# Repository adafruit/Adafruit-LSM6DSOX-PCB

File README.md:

## Adafruit LSM6DSOX 6-DoF Accelerometer and Gyro PCB

<a href="http://www.adafruit.com/products/4438"><br/>
Click here to purchase one from the Adafruit shop</a>

PCB files for the Adafruit LSM6DSOX 6-DoF Accelerometer and Gyro. 

Format is EagleCAD schematic and board layout
* https://www.adafruit.com/product/4438

### Description

INSERT PRODUCT COPY HERE

### License

Adafruit invests time and resources providing this open source design, please support Adafruit and open-source hardware by purchasing products from [Adafruit](https://www.adafruit.com)!

Designed by Bryan Siepert for Adafruit Industries.

Creative Commons Attribution/Share-Alike, all text above must be included in any redistribution. 
See license.txt for additional details.

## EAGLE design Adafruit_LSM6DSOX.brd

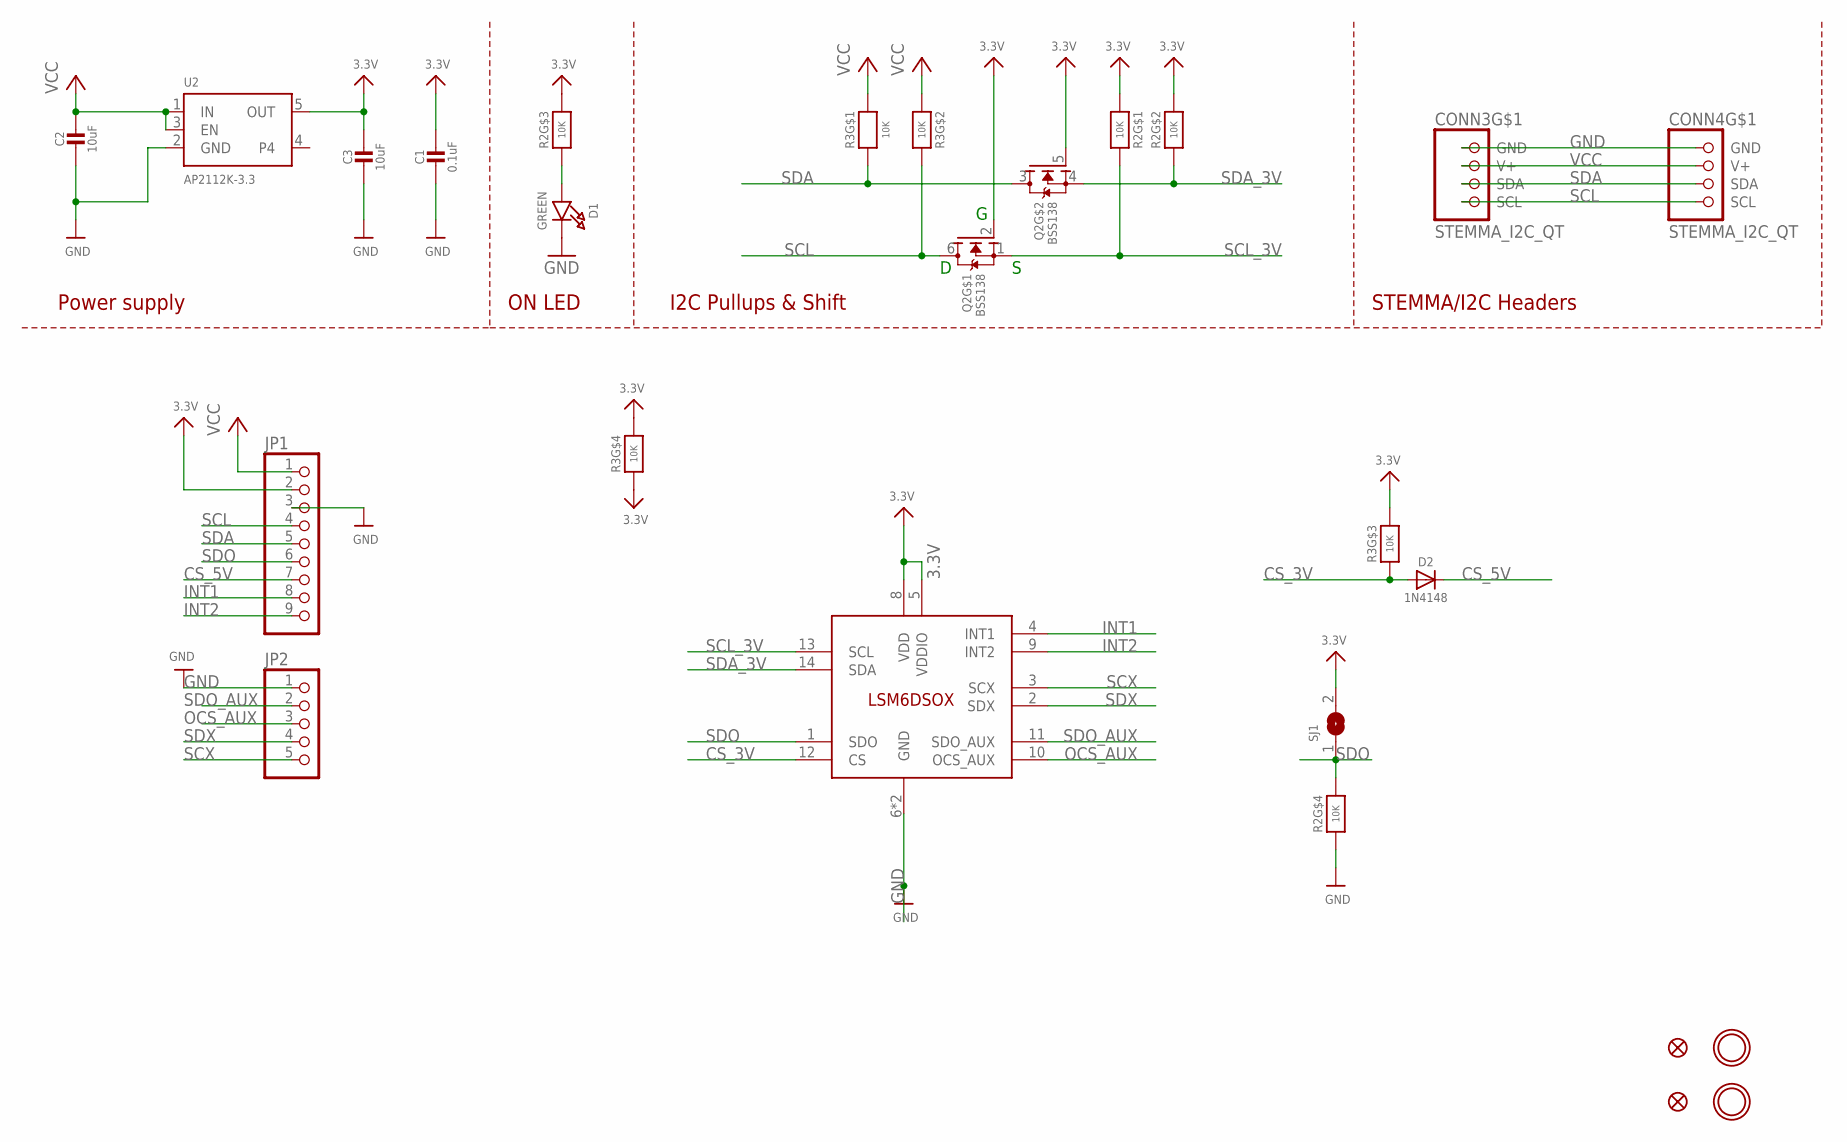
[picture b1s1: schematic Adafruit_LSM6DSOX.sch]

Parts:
C1: 0.1uF; 0603-NO
C2, C3: 10uF; 0805-NO
CONN3, CONN4: STEMMA_I2C_QT; JST_SH4
D1: GREEN; CHIPLED_0603_NOOUTLINE
D2: 1N4148; SOD-323
FID3, FID4: FIDUCIAL_1MM
JP1: HEADER-1X970MIL; 1X09_ROUND_70
JP2: HEADER-1X570MIL; 1X05_ROUND_70
Q2: BSS138; SOT363
R2, R3: 10K; RESPACK_4X0603
SJ1: SOLDERJUMPER; SOLDERJUMPER_ARROW_NOPASTE
U2: AP2112K-3.3; SOT23-5
U$1, U$17: MOUNTINGHOLE2.5; MOUNTINGHOLE_2.5_PLATED
U$2: LSM6DSOX; LGA-14L

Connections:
3.3V: C1.1, C3.1, JP1.2, Q2.2 (G), Q2.5 (G), R2.1, R2.2 (1), R2.6 (2), R3.3 (1), R3.4 (1), R3.5 (2), SJ1.2, U2.5 (OUT), U$2.5 (VDDIO), U$2.8 (VDD)
CS_3V: D2.A, R3.6 (2), U$2.12 (CS)
CS_5V: D2.C, JP1.7
GND: C1.2, C2.2, C3.2, CONN3.1 (GND), CONN4.1 (GND), D1.C, JP1.3, JP2.1, R2.4 (1), U2.2 (GND), U$2.6 (GND), U$2.7 (GND)
INT1: JP1.8, U$2.4 (INT1)
INT2: JP1.9, U$2.9 (INT2)
unnamed: D1.A, R2.3 (1)
OCS_AUX: JP2.3, U$2.10 (OCS_AUX)
SCL: CONN3.4 (SCL), CONN4.4 (SCL), JP1.4, Q2.6 (D), R3.2 (1)
SCL_3V: Q2.1 (S), R2.8 (2), U$2.13 (SCL)
SCX: JP2.5, U$2.3 (SCX)
SDA: CONN3.3 (SDA), CONN4.3 (SDA), JP1.5, Q2.3 (D), R3.1
SDA_3V: Q2.4 (S), R2.7 (2), U$2.14 (SDA)
SDO: JP1.6, R2.5 (2), SJ1.1, U$2.1 (SDO)
SDO_AUX: JP2.2, U$2.11 (SDO_AUX)
SDX: JP2.4, U$2.2 (SDX)
VCC: C2.1, CONN3.2 (V+), CONN4.2 (V+), JP1.1, R3.7 (2), R3.8 (2), U2.1 (IN), U2.3 (EN)

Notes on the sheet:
I2C Pullups & Shift
STEMMA/I2C Headers
ON LED
Power supply

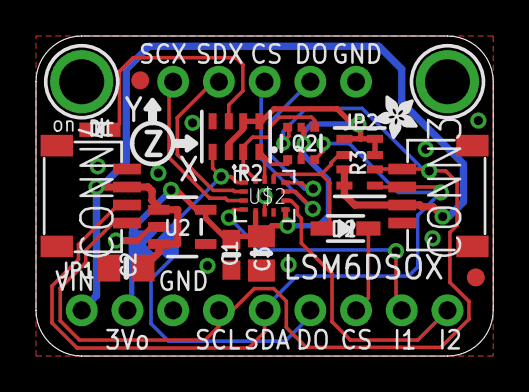
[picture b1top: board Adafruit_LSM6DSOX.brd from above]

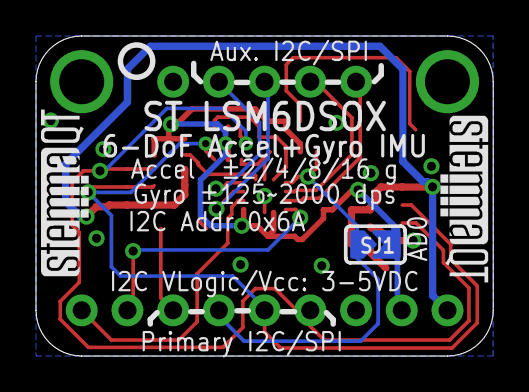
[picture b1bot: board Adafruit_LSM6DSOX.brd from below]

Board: 2 copper layers, 25.4 x 17.8 mm, 23 parts (4 on the bottom side), 17 nets.

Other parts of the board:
U$9: ADAFRUIT_2.5MM
U$25: PCBFEAT-REV-040
U$30, U$31: STEMMAQT

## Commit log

2019-12-04 initial commit, needs copy update and pic
2020-09-07 Fixed product image

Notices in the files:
parts and their libraries:
microbuilder: This work is placed in the public domain, and may be freely used for commercial and non-commercial work with the following conditions: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
